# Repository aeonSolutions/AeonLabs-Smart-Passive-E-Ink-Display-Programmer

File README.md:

[PCB-Prototyping-Catalogue](https://github.com/aeonSolutions/PCB-Prototyping-Catalogue)  >>  [Smart LCD Touch Displays](https://github.com/aeonSolutions/PCB-Prototyping-Catalogue/tree/main/Smart%20LCD%20Touch%20Displays)  >>  Smart Passive E-Ink Display Programmer

<br>

# Smart Passive E-Ink Display Programmer
 A PCB for programming E-Ink Displays. Plug the E-Ink Display to this PCB using magnetic pogo pins to upload a new static image to it.

*Don't forget to LIKE , SHARE and subscribe the free whatsApp group* and if you liked this PCB consider buying me a cup of coffee. Links below.

### Status
  Waiting for first batch from factory. Not tested.

If you already tested this PCB send me a message. Thank you

## Versions
- revision 2.x (ToDo)
  - Android App to view and control the E-Ink passive Display

- revison 1.x
  - PCB for programming E-Ink Passive Displays

PCB fabrication of June 2022 (reviision 1.1) was sponsored by [PCBWay](www.pcbway.com)

### alternatively if you do not want to build a PCB by yourself, you can buy here:

The price will be around 30eur plus postage fees.
(I will also deliver the assembled PCB with all the components in place at an aditonal cost).

## Liked it ? Get a Free PCB for yourself
Send me your Device or hardware and i will design a custom PCB for it. Free of charge. Contact-me on WhatsApp or email for more info. 

## Q&A WhatsApp Group
If you have any Questions or simply  like this kind of projects and want to stay updated with the latest research ideas and prototypes during the day and week, join the WhatsApp Group
[LDAD Lab & Prototyping](https://chat.whatsapp.com/FkNC7u83kuy2QRA5sqjBVg)

________________________________________________________________________________________________________________
## [Go back to main catalogue page](https://github.com/aeonSolutions/PCB-Prototyping-Catalogue)
________________________________________________________________________________________________________________

#### PCB Parts list:
- 2.13" E-Ink Display: https://s.click.aliexpress.com/e/_9gJUhJ
- FPC 24 pin connector: https://s.click.aliexpress.com/e/_AEUWtr
- FPC 10 pint connector: https://s.click.aliexpress.com/e/_AEUWtr
- SMD capacitors: https://s.click.aliexpress.com/e/_Asa5qd

<br />
<br />

______________________________________________________________________________________________________________________________

### PCB Conceptualization and Design
<p align="center">

</p>

<br />
<br />

### PCB Fabrication
<p align="center">

</p>

<br />
<br />

## Author

You can get in touch with me on my LinkedIn Profile:

#### Miguel Tomas

You can also follow my GitHub Profile to stay updated about my latest projects: 

<br>

### Be supportive of my dedication and work towards technology education and buy me a cup of coffee
The PCB Desgin Files i provide here for anyone to use are free. If you like this Smart Device or use it, please consider buying me a cup of coffee, a slice of pizza or a book to help me study, eat and think new PCB design files.

<p align+"left">

<br>

</p>

<br />

### Make a donation on Paypal
Make a donation on paypal and get a TAX refund*.

<br>

### Support all these open hardware projects and become a patreon  
Liked any of my PCB KiCad Designs? Help and Support my open work to all by becomming a LDAD Patreon.
In return I will give a free PCB design in KiCad to all patreon supporters. To learn more go to patreon.com. Link below.

<br />
<br />

______________________________________________________________________________________________________________________________
### License

Before proceeding to download any of AeonLabs software solutions for open-source development and/or PCB hardware electronics development make sure you are choosing the right license for your project. See [AeonLabs Solutions for Open Hardware & Source Development](https://github.com/aeonSolutions/PCB-Prototyping-Catalogue/wiki/AeonLabs-Solutions-for-Open-Hardware-&-Source-Development) for more information. 

______________________________________________________________________________________________________________________________

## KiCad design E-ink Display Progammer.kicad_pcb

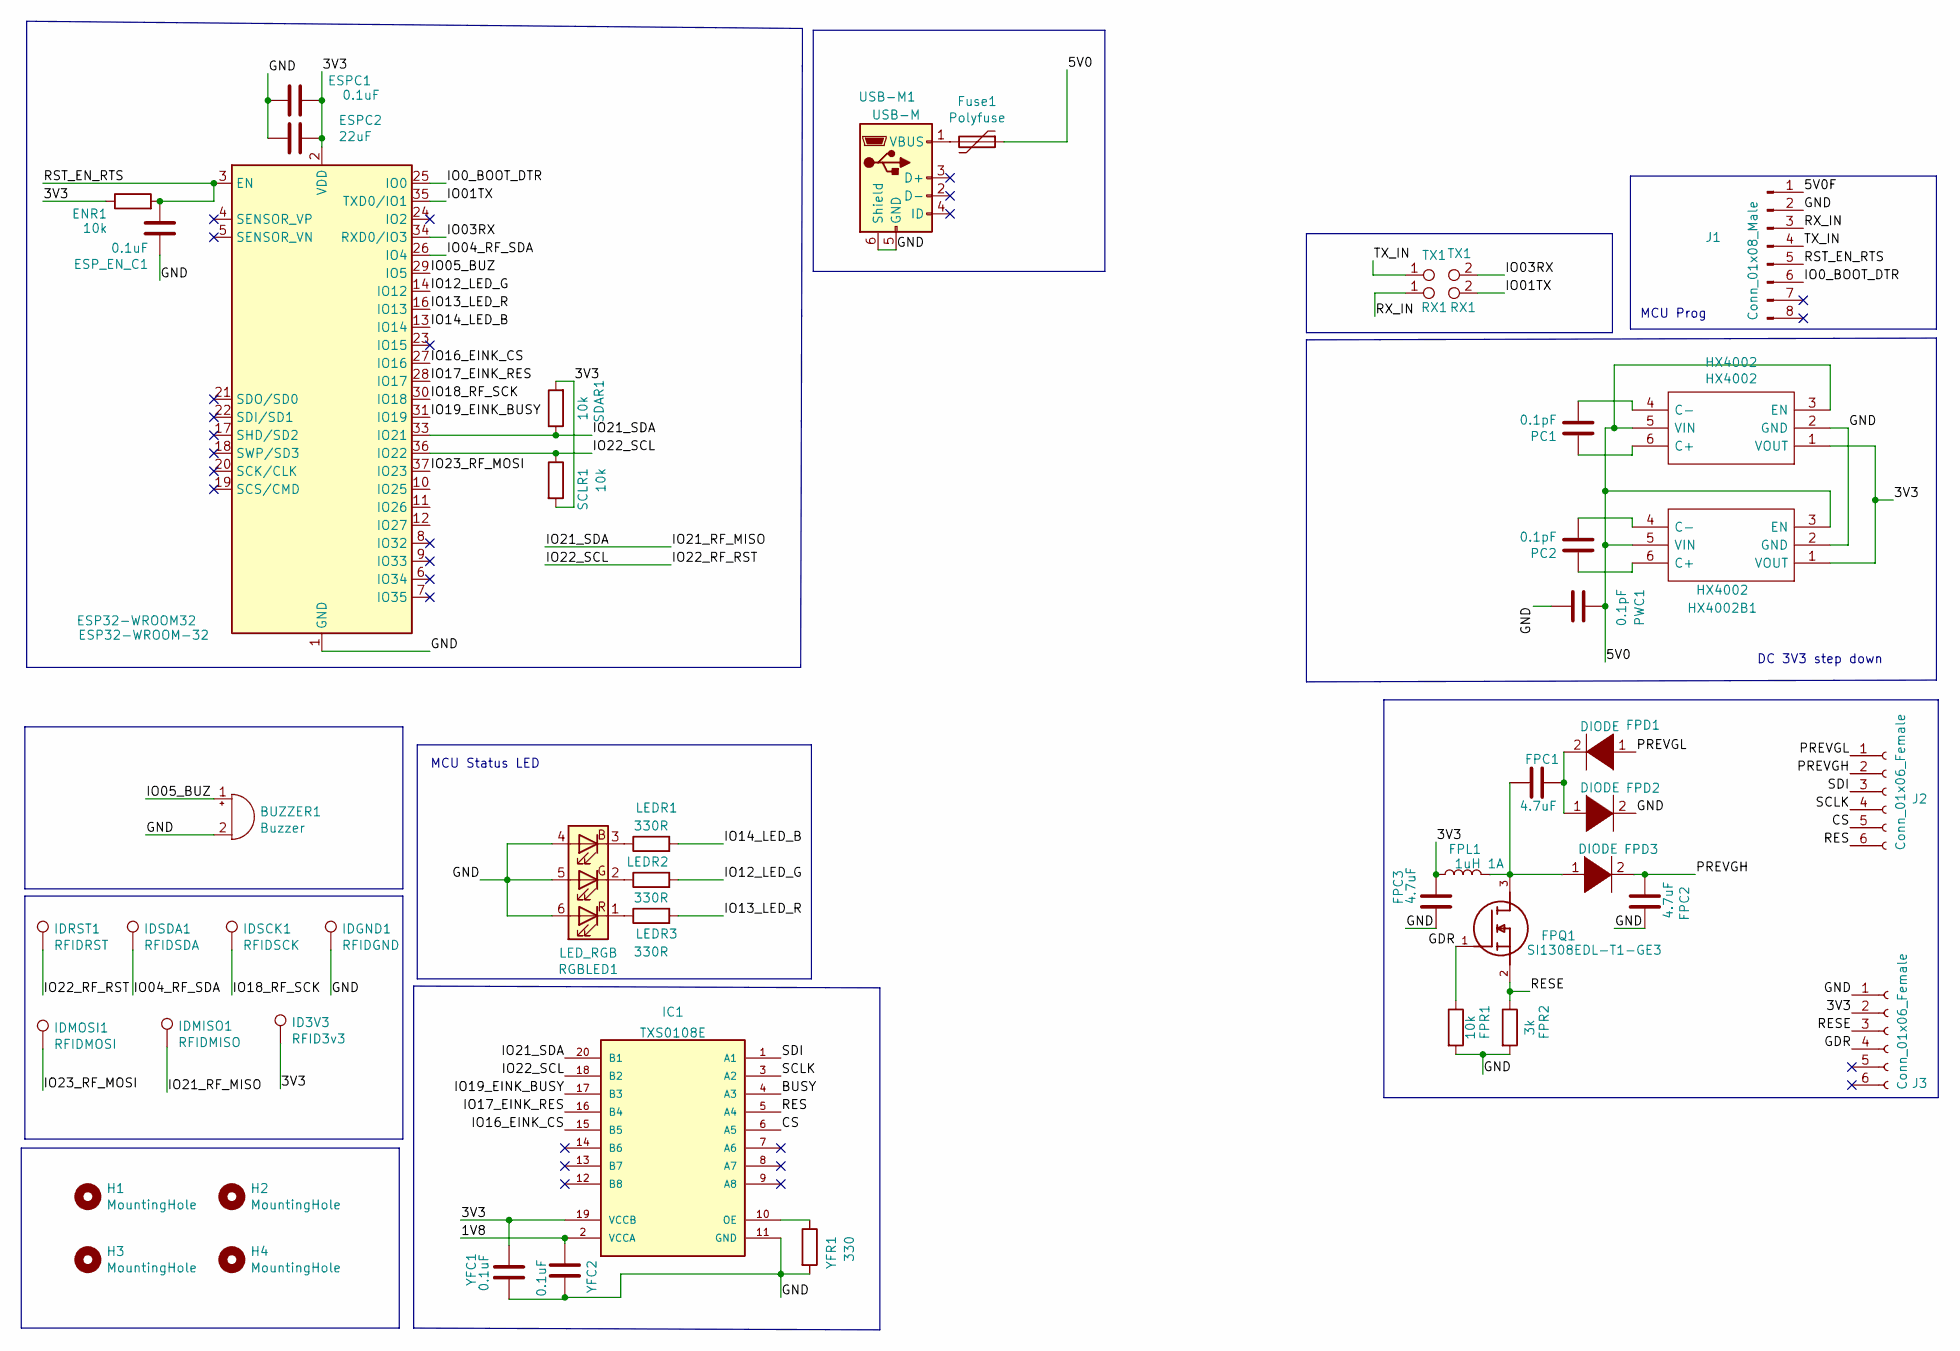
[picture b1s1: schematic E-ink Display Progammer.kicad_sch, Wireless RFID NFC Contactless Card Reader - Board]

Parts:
BUZZER1: Buzzer; MagneticBuzzer_Kobitone_254-EMB84Q-RO
ENR1: 10k; R_1206_3216MetricTrue
ESP32-WROOM32: ESP32-WROOM-32
ESPC1: 0.1uF; C_1206_3216MetricTrue
ESPC2: 22uF; C_1206_3216MetricTrue
ESP_EN_C1: 0.1uF; C_1206_3216MetricTrue
FPC1, FPC2, FPC3: 4.7uF; C_1206_3216MetricTrue
FPD1, FPD2, FPD3: DIODE; C_1206_3216MetricTrue
FPL1: 1uH 1A; C_1210_3225Metric_Pad1.33x2.70mm_HandSolder
FPQ1: SI1308EDL-T1-GE3; SI1308EDL-T1-GE3_SOT65P210X110-3N; Mouser_Part_Number 78-SI1308EDL-T1-GE3
FPR1: 10k; R_1206_3216MetricTrue
FPR2: 3k; R_1206_3216MetricTrue
Fuse1: Polyfuse; Fuse_1206_3216Metric_Pad1.42x1.75mm_HandSolder
H1, H2, H3, H4: MountingHole; MountingHole_6.5mm
HX4002, HX4002B1: HX4002; HX4002 SOT95 P280X125-6N; Manufacturer_Part_Number HX4002
IC1: TXS0108E; TXS0108E_YF08E_PW_R-PDSO-G20
ID3V3: RFID3v3; TestPoint_THTPad_2.0x2.0mm_Drill1.0mm
IDGND1: RFIDGND; TestPoint_THTPad_2.0x2.0mm_Drill1.0mm
IDMISO1: RFIDMISO; TestPoint_THTPad_2.0x2.0mm_Drill1.0mm
IDMOSI1: RFIDMOSI; TestPoint_THTPad_2.0x2.0mm_Drill1.0mm
IDRST1: RFIDRST; TestPoint_THTPad_2.0x2.0mm_Drill1.0mm
IDSCK1: RFIDSCK; TestPoint_THTPad_2.0x2.0mm_Drill1.0mm
IDSDA1: RFIDSDA; TestPoint_THTPad_2.0x2.0mm_Drill1.0mm
J1: Conn_01x08_Male; SOIC_clipProgSmall
J2, J3: Conn_01x06_Female; pogo 6pin magnetic
LEDR1, LEDR2, LEDR3: 330R; R_1206_3216Metric_Pad1.30x1.75mm_HandSolder
PC1, PC2: 0.1pF; C_1206_3216Metric_Pad1.33x1.80mm_HandSolder
PWC1: 0.1pF; C_1206_3216Metric_Pad1.33x1.80mm_HandSolder
RGBLED1: LED_RGB; LED_RGB_5050-6
RX1: RX1; TestPoint_Pad_Bridge_1.0x1.0mm
SCLR1: 10k; R_1206_3216MetricTrue
SDAR1: 10k; R_1206_3216MetricTrue
TX1: TX1; TestPoint_Pad_Bridge_1.0x1.0mm
USB-M1: USB-M; Micro_USB_pcb_socket_5pin_4weld_points
YFC1, YFC2: 0.1uF; C_1206_3216MetricTrue
YFR1: 330; R_1206_3216MetricTrue

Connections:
/1V8: IC1.2 (VCCA), YFC2.1
/3V3: ENR1.1, ESP32-WROOM32.2 (VDD), ESPC1.1, ESPC2.1, FPC3.1, FPL1.1, HX4002.1 (VOUT), HX4002B1.1 (VOUT), IC1.19 (VCCB), ID3V3.1, J3.2, SCLR1.2, SDAR1.2, YFC1.1
/5V0: Fuse1.1, HX4002.3 (EN), HX4002.5 (VIN), HX4002B1.3 (EN), HX4002B1.5 (VIN), PWC1.1
/5V0F: J1.1
/BUSY: IC1.4 (A3)
/CS: IC1.6 (A5), J2.5
/GDR: FPQ1.1, FPR1.1, J3.4
/GND: BUZZER1.2 (+), ESP32-WROOM32.1 (GND), ESP32-WROOM32.15 (GND), ESP32-WROOM32.38 (GND), ESP32-WROOM32.39 (GND), ESPC1.2, ESPC2.2, ESP_EN_C1.1, FPC2.2, FPC3.2, FPD2.2 (A), FPR1.2, FPR2.2, HX4002.2 (GND), HX4002B1.2 (GND), IC1.11 (GND), IDGND1.1, J1.2, J3.1, PWC1.2, RGBLED1.4 (BA), RGBLED1.5 (GA), RGBLED1.6 (RA), USB-M1.5 (GND), USB-M1.6 (Shield), YFC1.2, YFC2.2, YFR1.2
/IO0_BOOT_DTR: ESP32-WROOM32.25 (IO0), J1.6
/IO01TX: ESP32-WROOM32.35 (TXD0/IO1), RX1.2
/IO03RX: ESP32-WROOM32.34 (RXD0/IO3), TX1.2
/IO04_RF_SDA: ESP32-WROOM32.26 (IO4), IDSDA1.1
/IO05_BUZ: BUZZER1.1 (-), ESP32-WROOM32.29 (IO5)
/IO12_LED_G: ESP32-WROOM32.14 (IO12), LEDR2.2
/IO13_LED_R: ESP32-WROOM32.16 (IO13), LEDR3.2
/IO14_LED_B: ESP32-WROOM32.13 (IO14), LEDR1.2
/IO16_EINK_CS: ESP32-WROOM32.27 (IO16), IC1.15 (B5)
/IO17_EINK_RES: ESP32-WROOM32.28 (IO17), IC1.16 (B4)
/IO18_RF_SCK: ESP32-WROOM32.30 (IO18), IDSCK1.1
/IO19_EINK_BUSY: ESP32-WROOM32.31 (IO19), IC1.17 (B3)
/IO21_RF_MISO: ESP32-WROOM32.33 (IO21), IC1.20 (B1), IDMISO1.1, SDAR1.1
/IO22_RF_RST: ESP32-WROOM32.36 (IO22), IC1.18 (B2), IDRST1.1, SCLR1.1
/IO23_RF_MOSI: ESP32-WROOM32.37 (IO23), IDMOSI1.1
/PREVGH: FPC2.1, FPD3.2 (A), J2.2
/PREVGL: FPD1.1 (K), J2.1
/RES: IC1.5 (A4), J2.6
/RESE: FPQ1.2, FPR2.1, J3.3
/RST_EN_RTS: ENR1.2, ESP32-WROOM32.3 (EN), ESP_EN_C1.2, J1.5
/RX_IN: J1.3, RX1.1
/SCLK: IC1.3 (A2), J2.4
/SDI: IC1.1 (A1), J2.3
/TX_IN: J1.4, TX1.1
unnamed: FPC1.1, FPD1.2 (A), FPD2.1 (K)
unnamed: FPC1.2, FPD3.1 (K), FPL1.2, FPQ1.3
unnamed: Fuse1.2, USB-M1.1 (VBUS)
unnamed: HX4002.4 (C-), PC1.2
unnamed: HX4002.6 (C+), PC1.1
unnamed: HX4002B1.4 (C-), PC2.2
unnamed: HX4002B1.6 (C+), PC2.1
unnamed: IC1.10 (OE), YFR1.1
unnamed: LEDR1.1, RGBLED1.3 (BK)
unnamed: LEDR2.1, RGBLED1.2 (GK)
unnamed: LEDR3.1, RGBLED1.1 (RK)

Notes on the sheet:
DC 3V3 step down
MCU Prog
MCU Status LED

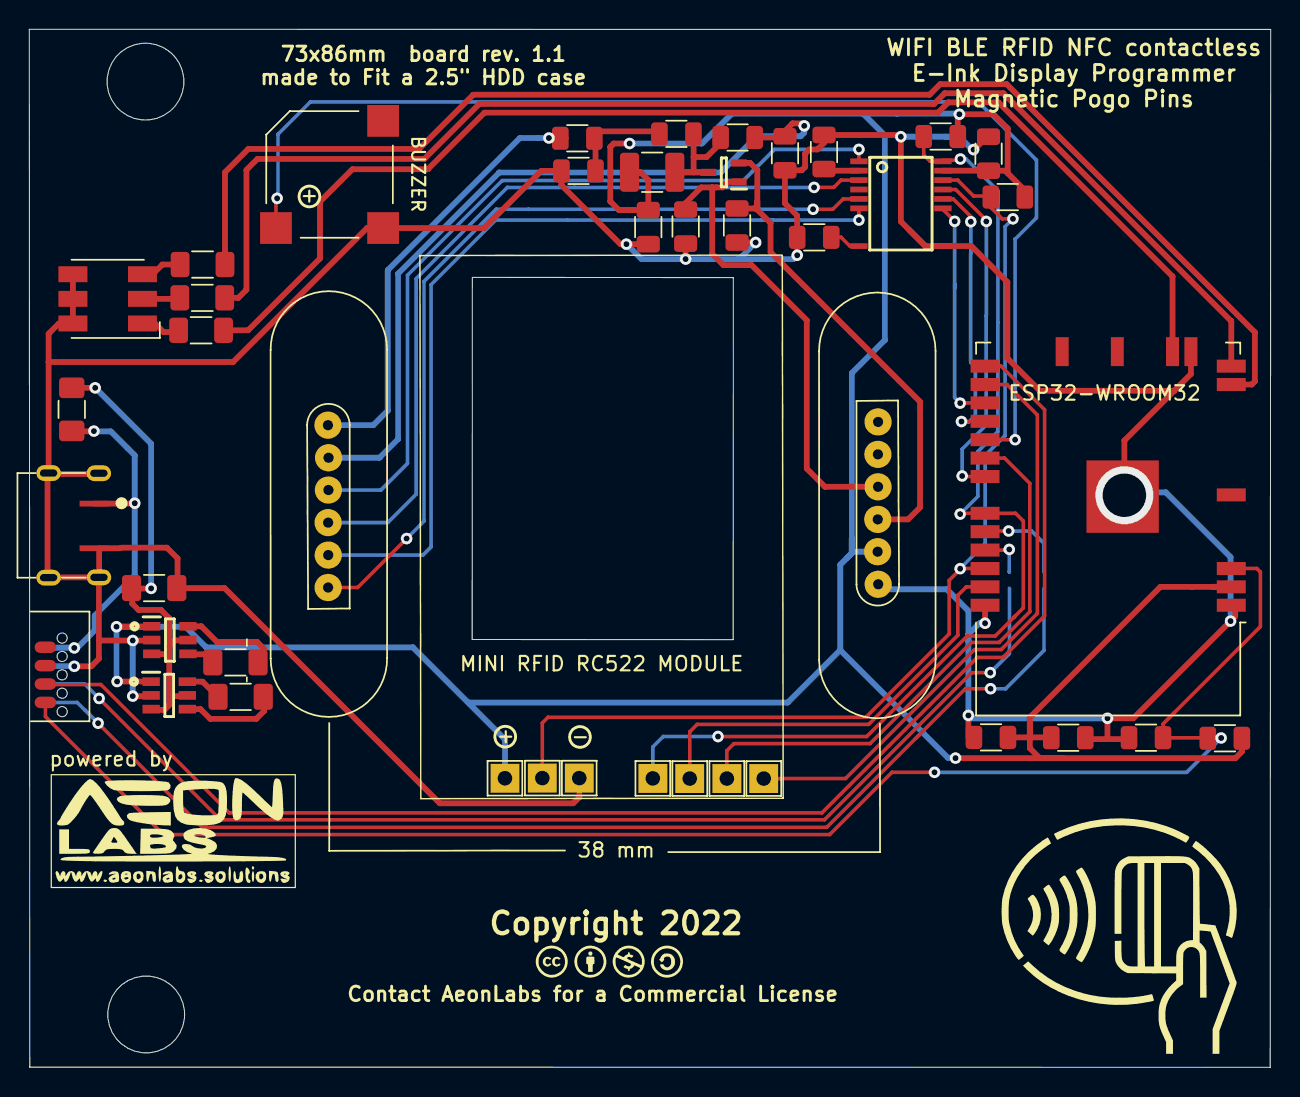
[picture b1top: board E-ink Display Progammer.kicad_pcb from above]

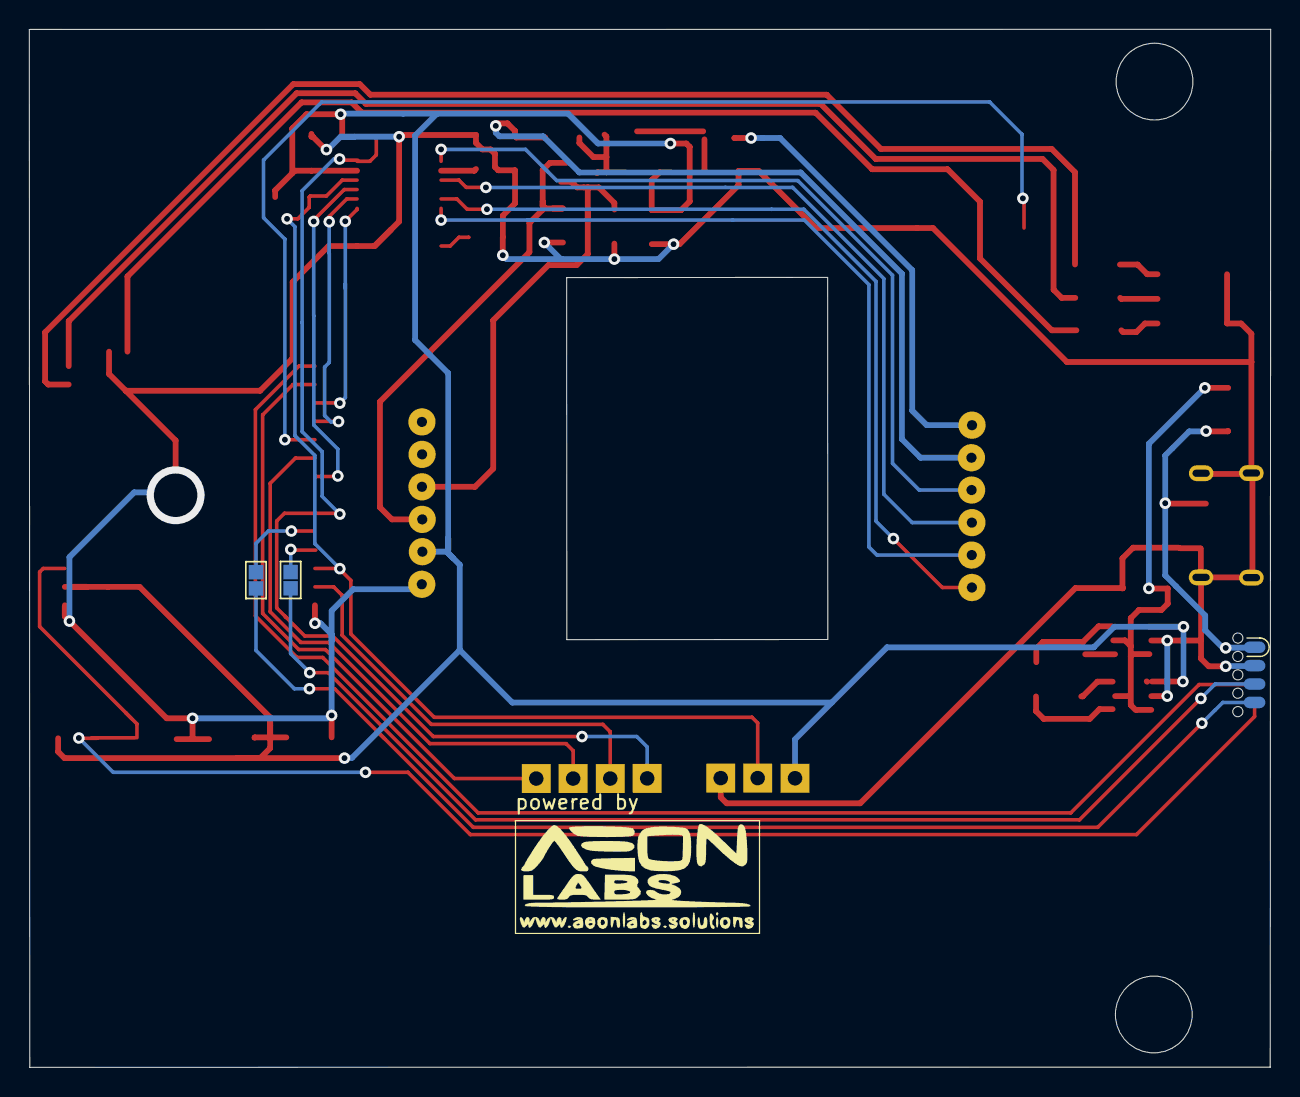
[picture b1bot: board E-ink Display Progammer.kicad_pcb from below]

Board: 2 copper layers, 85.7 x 71.7 mm, 49 parts (3 on the bottom side), 41 nets.

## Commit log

2022-05-11 rev 1.0
2022-05-12 rev 1.1

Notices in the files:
E-ink Display Progammer.kicad_pcb:
Copyright 2022
